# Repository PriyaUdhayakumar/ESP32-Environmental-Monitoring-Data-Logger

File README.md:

# ESP32 Environmental Monitoring Data Logger

## Project Overview

An ESP32-based environmental monitoring data logger developed using ESP-IDF and C.

The system is designed to collect environmental parameters from a BME280 sensor, obtain date and time information from a DS3231 RTC, and store the measurements on a microSD card in CSV format.

The firmware is organized into independent modules for sensor handling, RTC, SD card, logging, UART and LED control.

---

## System Architecture

```text
                 ┌──────────────┐
                 │    BME280    │
                 │ Temperature  │
                 │ Humidity     │
                 │ Pressure     │
                 └──────┬───────┘
                        │ I2C
                        │
                 ┌──────▼───────┐
                 │    ESP32     │
                 │              │
                 │  FreeRTOS    │
                 │    Logger    │
                 └───┬──────┬───┘
                     │      │
                  I2C│      │SPI
                     │      │
             ┌───────▼──┐ ┌─▼────────┐
             │  DS3231  │ │ MicroSD  │
             │   RTC    │ │  Card    │
             └──────────┘ └────┬─────┘
                               │
                               ▼
                           data.csv
Hardware
ESP32
BME280 Environmental Sensor
DS3231 Real-Time Clock
MicroSD Card
LED
USB/UART interface

Software
Embedded C
ESP-IDF
FreeRTOS
I2C
SPI
FAT filesystem
Git/GitHub
KiCad

Firmware Modules
main/
├── app_main.c
├── bme280.c
├── bme280.h
├── sensor.c
├── sensor.h
├── rtc.c
├── rtc.h
├── sdcard.c
├── sdcard.h
├── logger.c
├── logger.h
├── led.c
├── led.h
├── uart.c
└── uart.h

Module Description
BME280 – Interfaces with the environmental sensor.
Sensor – Provides a simple interface for sensor initialization and readings.
RTC – Interfaces with the DS3231 real-time clock.
SD Card – Handles microSD card initialization and file operations.
Logger – Combines sensor and RTC data and stores it on the SD card.
LED – Provides status indication.
UART – Provides serial communication/debugging.

current Status
 ESP-IDF project setup
 UART module
 BME280 module
 Sensor module
 DS3231 RTC module
 SD card SPI module
 CSV file creation
 CSV data append
 FreeRTOS logging task
 Prevent CSV overwrite on restart
 Hardware testing
 PCB design
 PCB manufacturing
 Long-duration logging test

Future Improvements
Hardware validation
Finalize logging interval
SD card error handling
Custom PCB using KiCad
Long-duration environmental data logging
Data analysis using the generated CSV files
Enclosure design

Project Goal

This project demonstrates practical skills in:

Embedded C programming
ESP32 and ESP-IDF development
FreeRTOS
I2C and SPI communication
Sensor interfacing
RTC interfacing
SD card data logging
Modular embedded firmware development
PCB design using KiCad

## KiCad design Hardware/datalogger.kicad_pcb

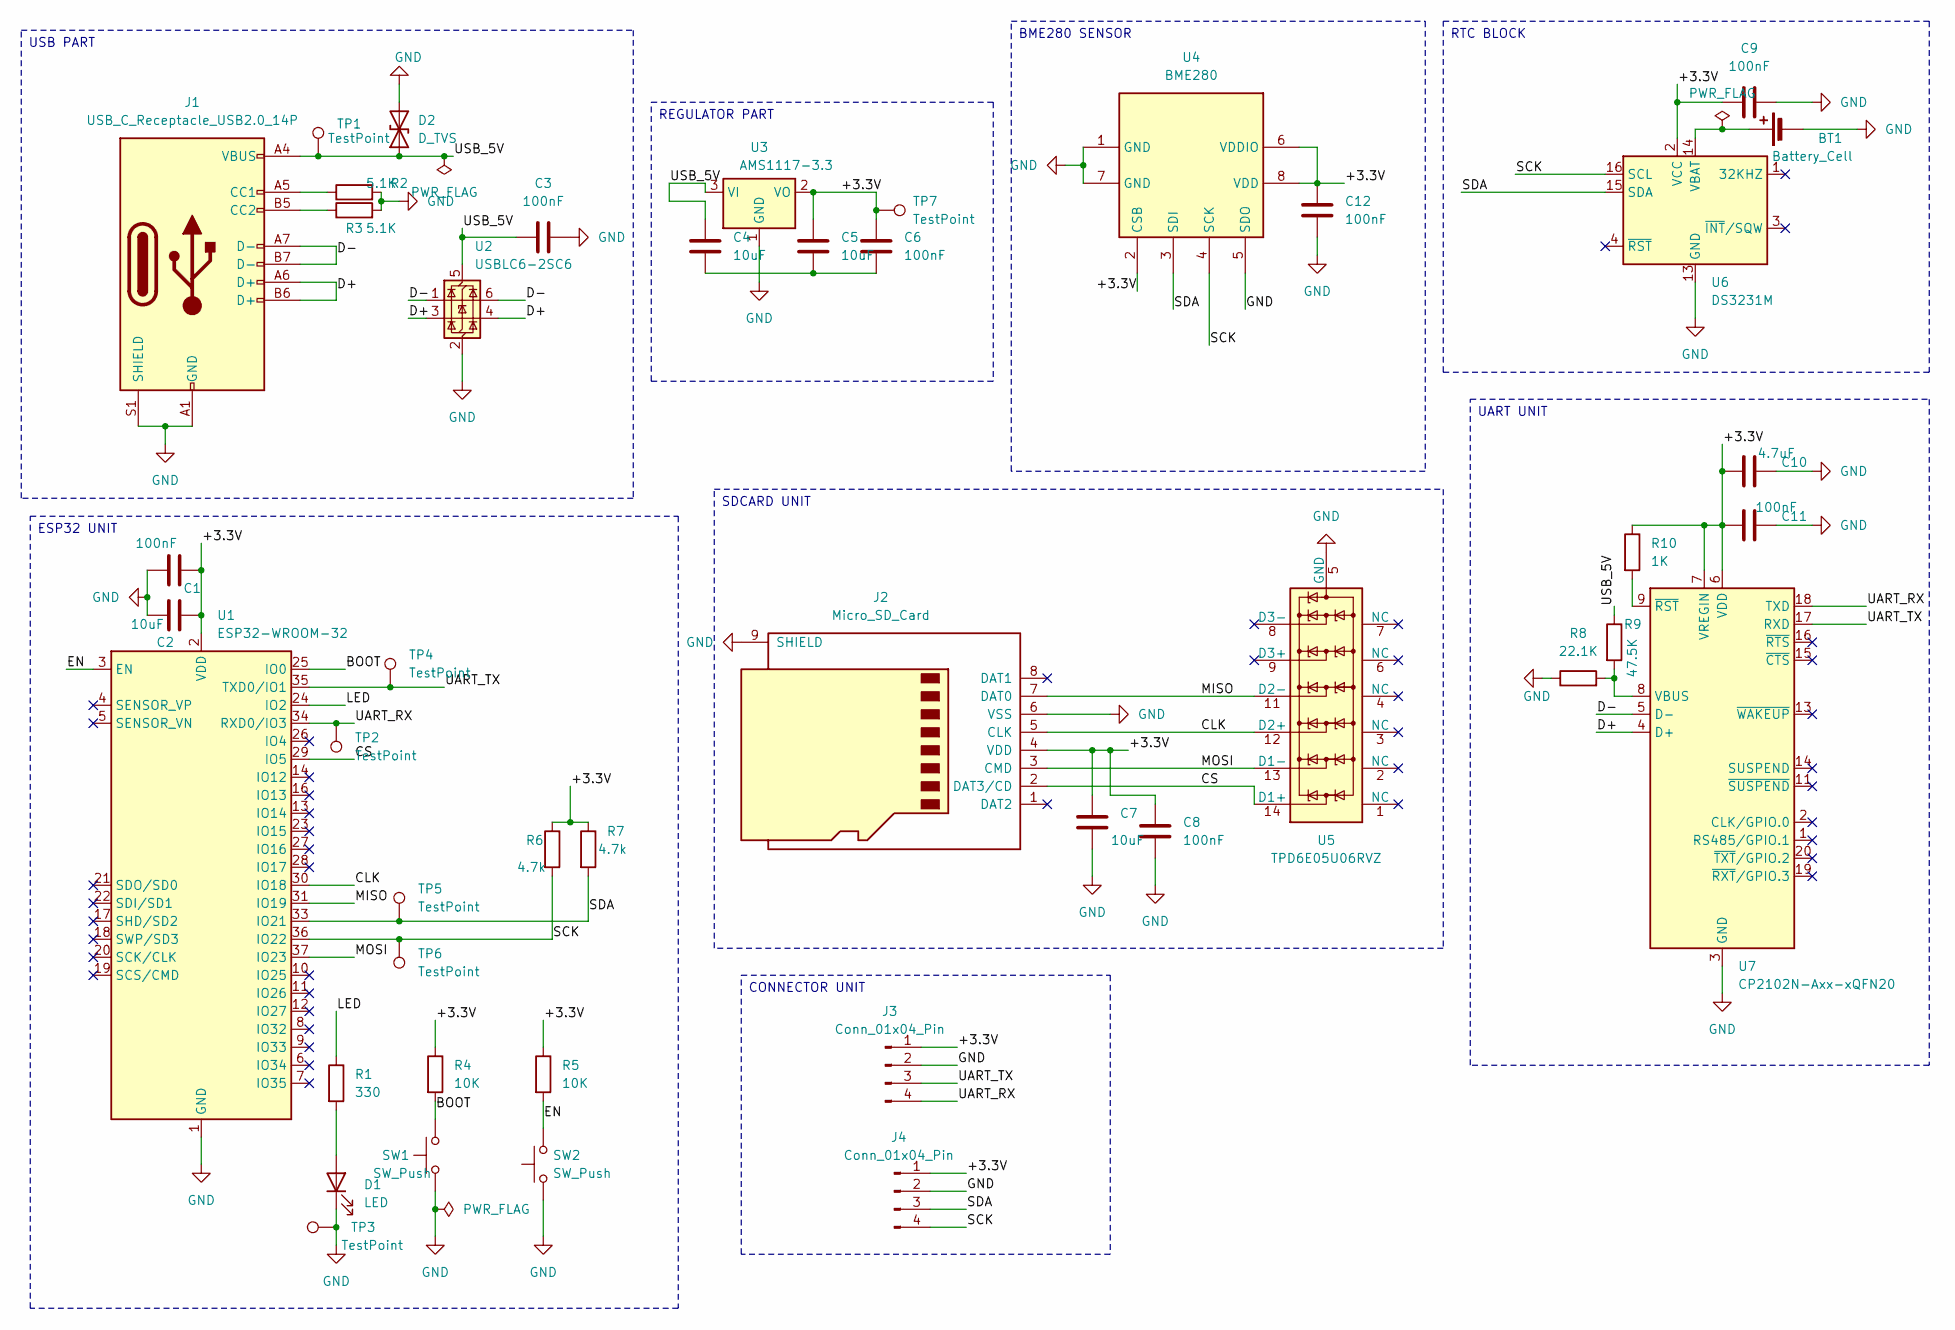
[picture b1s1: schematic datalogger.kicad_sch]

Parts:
BT1: Battery_Cell; BatteryHolder_Keystone_3002_1x2032
C1, C3, C6, C8, C9, C11, C12: 100nF; C_0805_2012Metric
C2, C4, C5, C7: 10uF; C_0805_2012Metric
C10: 4.7uF; C_0805_2012Metric
D1: LED; LED_0805_2012Metric
D2: D_TVS; D_SOD-323
J1: USB_C_Receptacle_USB2.0_14P; USB_C_Receptacle_GCT_USB4105-xx-A_16P_TopMnt_Horizontal
J2: Micro_SD_Card; microSD_HC_Hirose_DM3AT-SF-PEJM5
J3, J4: Conn_01x04_Pin; PinHeader_1x04_P2.54mm_Vertical
R1: 330; R_0805_2012Metric
R2, R3: 5.1K; R_0805_2012Metric
R4, R5: 10K; R_0805_2012Metric
R6, R7: 4.7k; R_0805_2012Metric
R8: 22.1K; R_0805_2012Metric
R9: 47.5K; R_0805_2012Metric
R10: 1K; R_0805_2012Metric
SW1, SW2: SW_Push; SW_SPST_TL3342
TP1, TP2, TP3, TP4, TP5, TP6, TP7: TestPoint; TestPoint_Pad_D2.0mm
U1: ESP32-WROOM-32
U2: USBLC6-2SC6; SOT-23-6
U3: AMS1117-3.3; SOT-223-3_TabPin2
U4: BME280; Bosch_LGA-8_2.5x2.5mm_P0.65mm_ClockwisePinNumbering
U5: TPD6E05U06RVZ; Texas_R-PUSON-N14
U6: DS3231M; SOIC-16W_7.5x10.3mm_P1.27mm
U7: CP2102N-Axx-xQFN20; SiliconLabs_QFN-20-1EP_3x3mm_P0.5mm_EP1.8x1.8mm

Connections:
/+3.3V: C1.2, C2.2, C5.1, C6.1, C7.2, C8.2, C9.1, C10.1, C11.1, C12.2, J2.4 (VDD), J3.1, J4.1, R4.1, R5.1, R6.1, R7.1, R10.1, TP7.1, U1.2 (VDD), U3.2 (VO), U4.2 (CSB), U4.6 (VDDIO), U4.8 (VDD), U6.2 (VCC), U7.6 (VDD), U7.7 (VREGIN)
/BOOT: R4.2, SW1.2, U1.25 (IO0)
/CLK: J2.5 (CLK), U1.30 (IO18), U5.12 (D2+)
/CS: J2.2 (DAT3/CD), U1.29 (IO5), U5.14 (D1+)
/D+: J1.A6 (D+), J1.B6 (D+), U2.3 (I/O2), U2.4 (I/O2), U7.4 (D+)
/D-: J1.A7 (D-), J1.B7 (D-), U2.1 (I/O1), U2.6 (I/O1), U7.5 (D-)
/EN: R5.2, SW2.2, U1.3 (EN)
/LED: R1.1, U1.24 (IO2)
/MISO: J2.7 (DAT0), U1.31 (IO19), U5.11 (D2-)
/MOSI: J2.3 (CMD), U1.37 (IO23), U5.13 (D1-)
/SCK: J4.4, R6.2, TP6.1, U1.36 (IO22), U4.4 (SCK), U6.16 (SCL)
/SDA: J4.3, R7.2, TP5.1, U1.33 (IO21), U4.3 (SDI), U6.15 (SDA)
/UART_RX: J3.4, TP2.1, U1.34 (RXD0/IO3), U7.18 (TXD)
/UART_TX: J3.3, TP4.1, U1.35 (TXD0/IO1), U7.17 (RXD)
/USB_5V: C3.1, C4.1, D2.1 (A1), J1.A4 (VBUS), J1.A9 (VBUS), J1.B4 (VBUS), J1.B9 (VBUS), R9.1, TP1.1, U2.5 (VBUS), U3.3 (VI)
GND: BT1.2 (-), C1.1, C2.1, C3.2, C7.1, C8.1, C9.2, C10.2, C11.2, C12.1, D1.1 (K), D2.2 (A2), J1.A1 (GND), J1.A12 (GND), J1.B1 (GND), J1.B12 (GND), J1.S1 (SHIELD), J2.6 (VSS), J2.9 (SHIELD), J3.2, J4.2, R2.2, R3.2, R8.1, SW1.1, SW2.1, TP3.1, U1.1 (GND), U1.15 (GND), U1.38 (GND), U1.39 (GND), U2.2 (GND), U3.1 (GND), U4.1 (GND), U4.5 (SDO), U4.7 (GND), U5.5 (GND), U5.10 (GND), U6.5 (GND), U6.6 (GND), U6.7 (GND), U6.8 (GND), U6.9 (GND), U6.10 (GND), U6.11 (GND), U6.12 (GND), U6.13 (GND), U7.3 (GND), U7.12 (GND), U7.21 (GND)
unnamed: BT1.1 (+), U6.14 (VBAT)
unnamed: C4.2, C5.2, C6.2
unnamed: D1.2 (A), R1.2
unnamed: J1.A5 (CC1), R2.1
unnamed: J1.B5 (CC2), R3.1
unnamed: R8.2, R9.2, U7.8 (VBUS)
unnamed: R10.2, U7.9 (~RST)

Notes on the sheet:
USB PART
RTC BLOCK
REGULATOR PART
ESP32 UNIT
BME280 SENSOR
SDCARD UNIT
CONNECTOR UNIT
UART UNIT

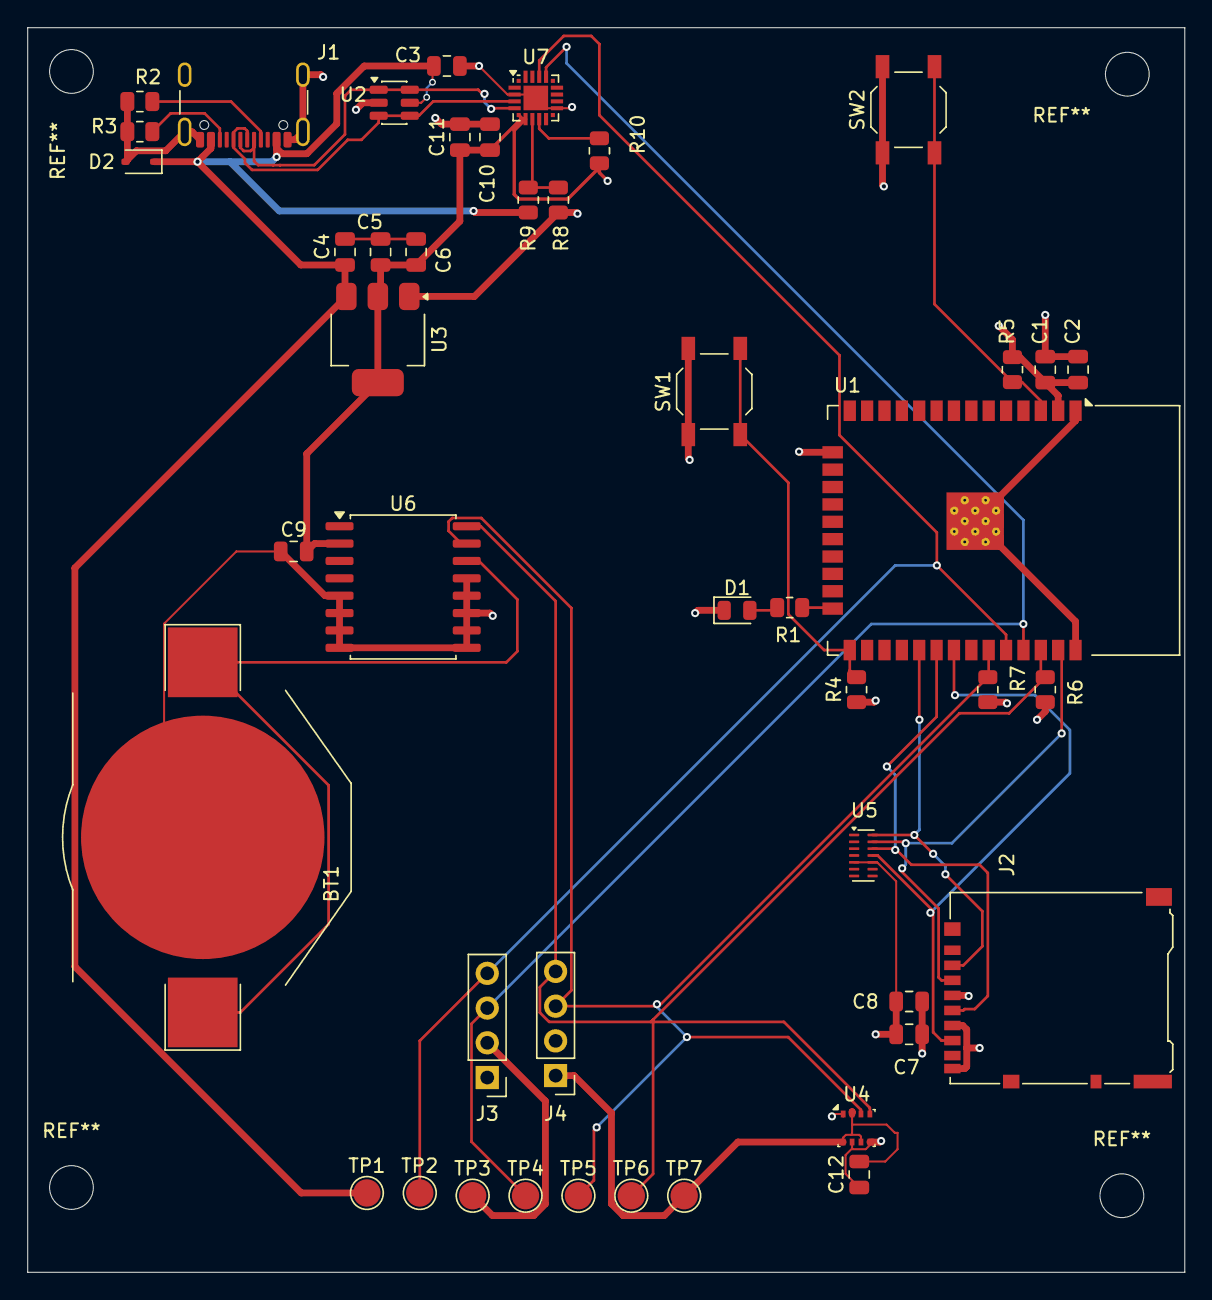
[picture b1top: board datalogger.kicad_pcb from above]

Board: 4 copper layers, 84.6 x 91.0 mm, 45 parts (0 on the bottom side), 23 nets.
